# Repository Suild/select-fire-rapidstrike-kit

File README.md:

# select-fire-rapidstrike-kit
Schematics, board files, and firmware for every variant of the Select-fire Rapidstrike Kit.

Buy Link: https://suild.com/shop/4

Grants reliable select-fire control to your Rapidstrike with optional rate of fire control using a knob. Like every other kit, this one is super simple to install and requires no soldering directly onto the board to get everything up and runing in under a minute, even easier than a regular RS mod!

Built-in pusher return and solenoid support makes this kit easily adaptable to any custom 3D-printed blaster. A powerful voltage regulator buck converter, on-board Arduino Nano, and breakout of power rails make this ideal for tinkerers and Makers who want to bring this kit one step farther. And everything is open-source.

I hope you find value in this. I personally learned a lot from open-source projects. I've included a PDF for every schematic and images of the top and bottom for every board so you can view them on mobile and without installing Eagle CAD.

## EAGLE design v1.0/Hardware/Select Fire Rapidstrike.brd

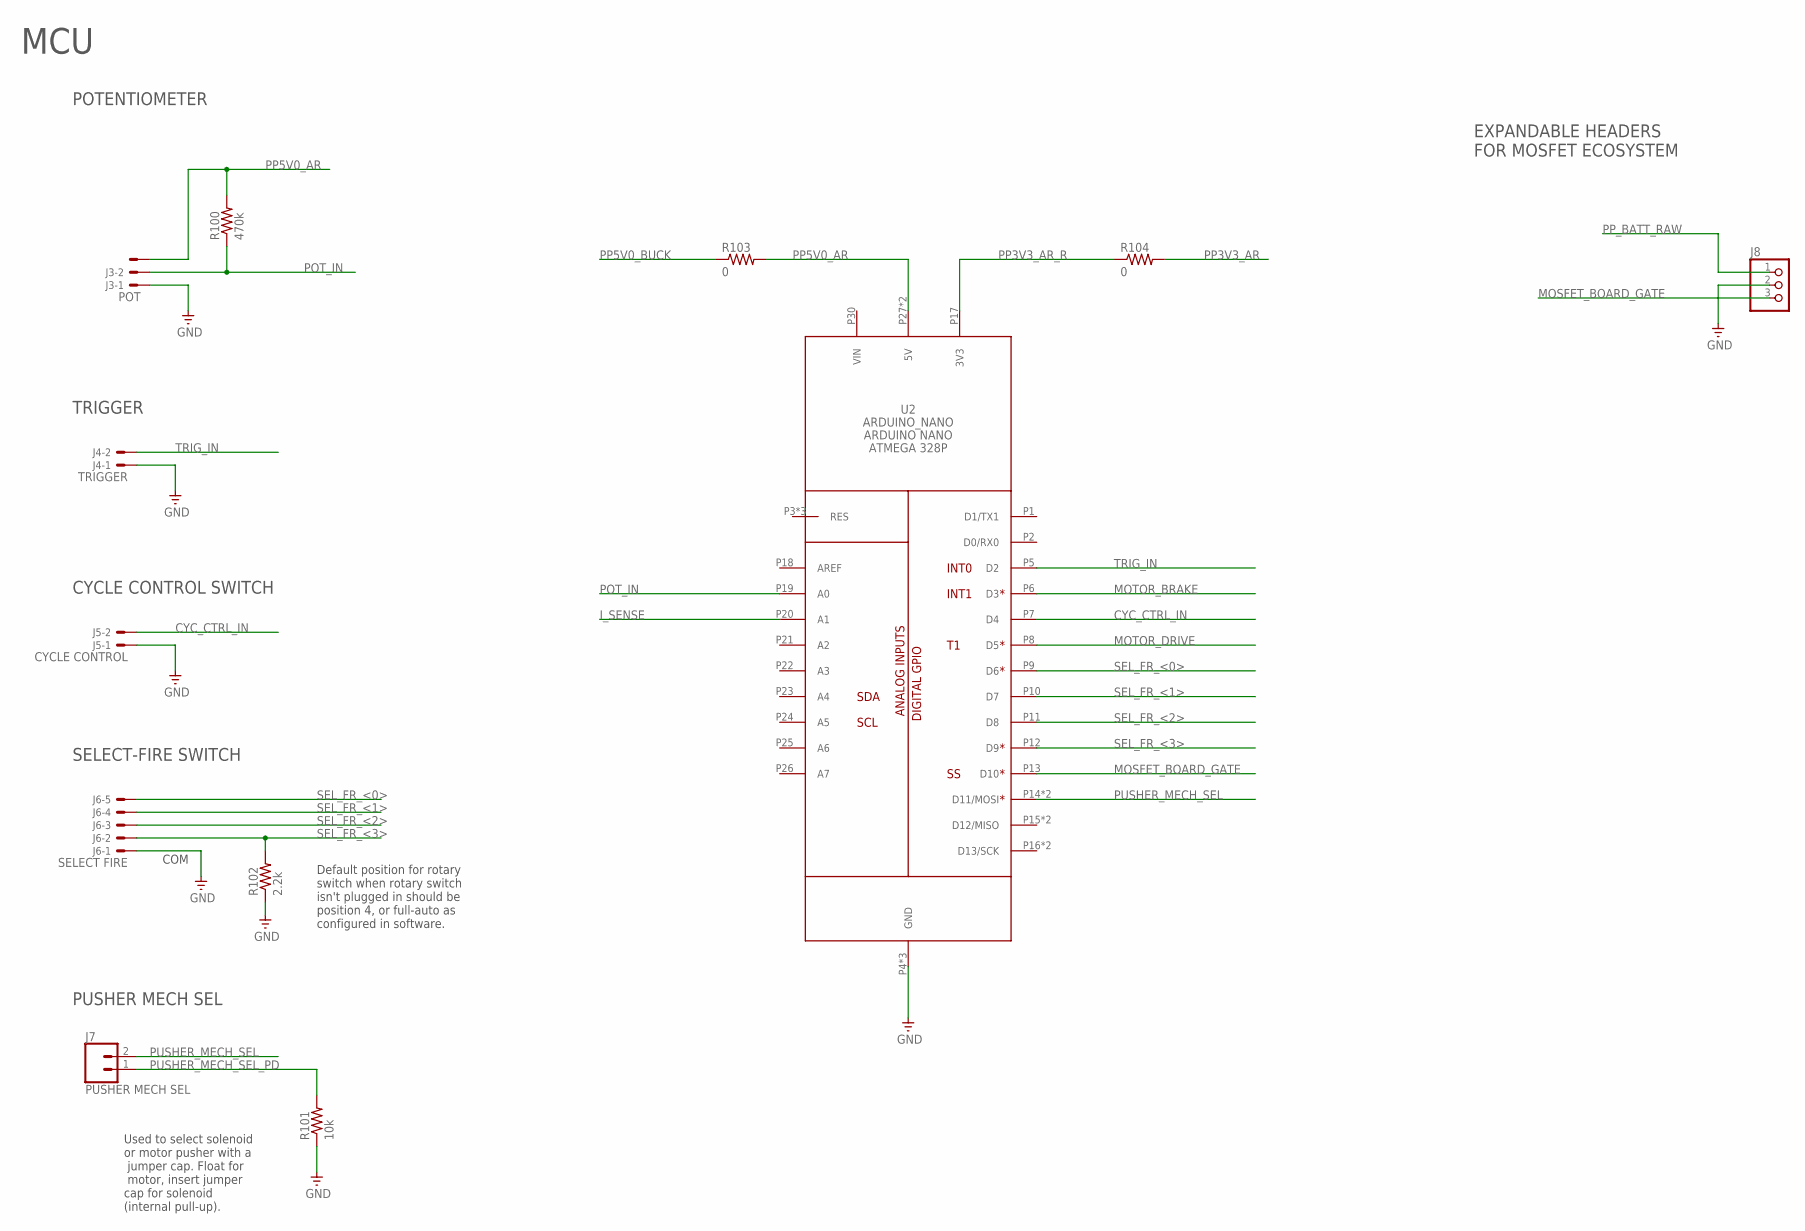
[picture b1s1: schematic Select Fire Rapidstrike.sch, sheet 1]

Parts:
J3: POT; JST-XH-03-PACKAGE-LONG-PAD
J4: TRIGGER; JST-XH-02-PACKAGE-LONG-PAD
J5: CYCLE CONTROL; JST-XH-02-PACKAGE-LONG-PAD
J6: SELECT FIRE; JST-XH-05-PACKAGE-LONG-PAD
J7: PUSHER MECH SEL; 1X02
J8: PINHD-1X3; 1X03
R100: 470k; M0805
R101: 10k; M0805
R102: 2.2k; M0805
R103, R104: 0; M0805
U2: ARDUINO_NANO

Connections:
CYC_CTRL_IN: J5.2, U2.P7 (D4)
GND: J3.1, J4.1, J5.1, J6.1, J8.2, R101.1, R102.1, U2.P4 (GND), U2.P29 (GND), U2.P32 (GND); also elsewhere on the board
I_SENSE: U2.P20 (A1); also elsewhere on the board
MOSFET_BOARD_GATE: J8.3, U2.P13 (D10)
MOTOR_BRAKE: U2.P6 (D3); also elsewhere on the board
MOTOR_DRIVE: U2.P8 (D5); also elsewhere on the board
POT_IN: J3.2, R100.1, U2.P19 (A0)
PP3V3_AR: R104.2; also elsewhere on the board
PP3V3_AR_R: R104.1, U2.P17 (3V3)
PP5V0_AR: J3.3, R100.2, R103.2, U2.P27 (5V), U2.P36 (5V); also elsewhere on the board
PP5V0_BUCK: R103.1; also elsewhere on the board
PP_BATT_RAW: J8.1; also elsewhere on the board
PUSHER_MECH_SEL: J7.2, U2.P14 (D11/MOSI), U2.P34 (D11/MOSI)
PUSHER_MECH_SEL_PD: J7.1, R101.2
SEL_FR_<0>: J6.5, U2.P9 (D6)
SEL_FR_<1>: J6.4, U2.P10 (D7)
SEL_FR_<2>: J6.3, U2.P11 (D8)
SEL_FR_<3>: J6.2, R102.2, U2.P12 (D9)
TRIG_IN: J4.2, U2.P5 (D2)

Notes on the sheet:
MCU
POTENTIOMETER
TRIGGER
CYCLE CONTROL SWITCH
SELECT-FIRE SWITCH
EXPANDABLE HEADERS FOR MOSFET ECOSYSTEM
PUSHER MECH SEL
Default position for rotary switch when rotary switch isn't plugged in should be position 4, or full-auto as configured in software.
Used to select solenoid or motor pusher with a jumper cap. Float for motor, insert jumper cap for solenoid (internal pull-up).
COM

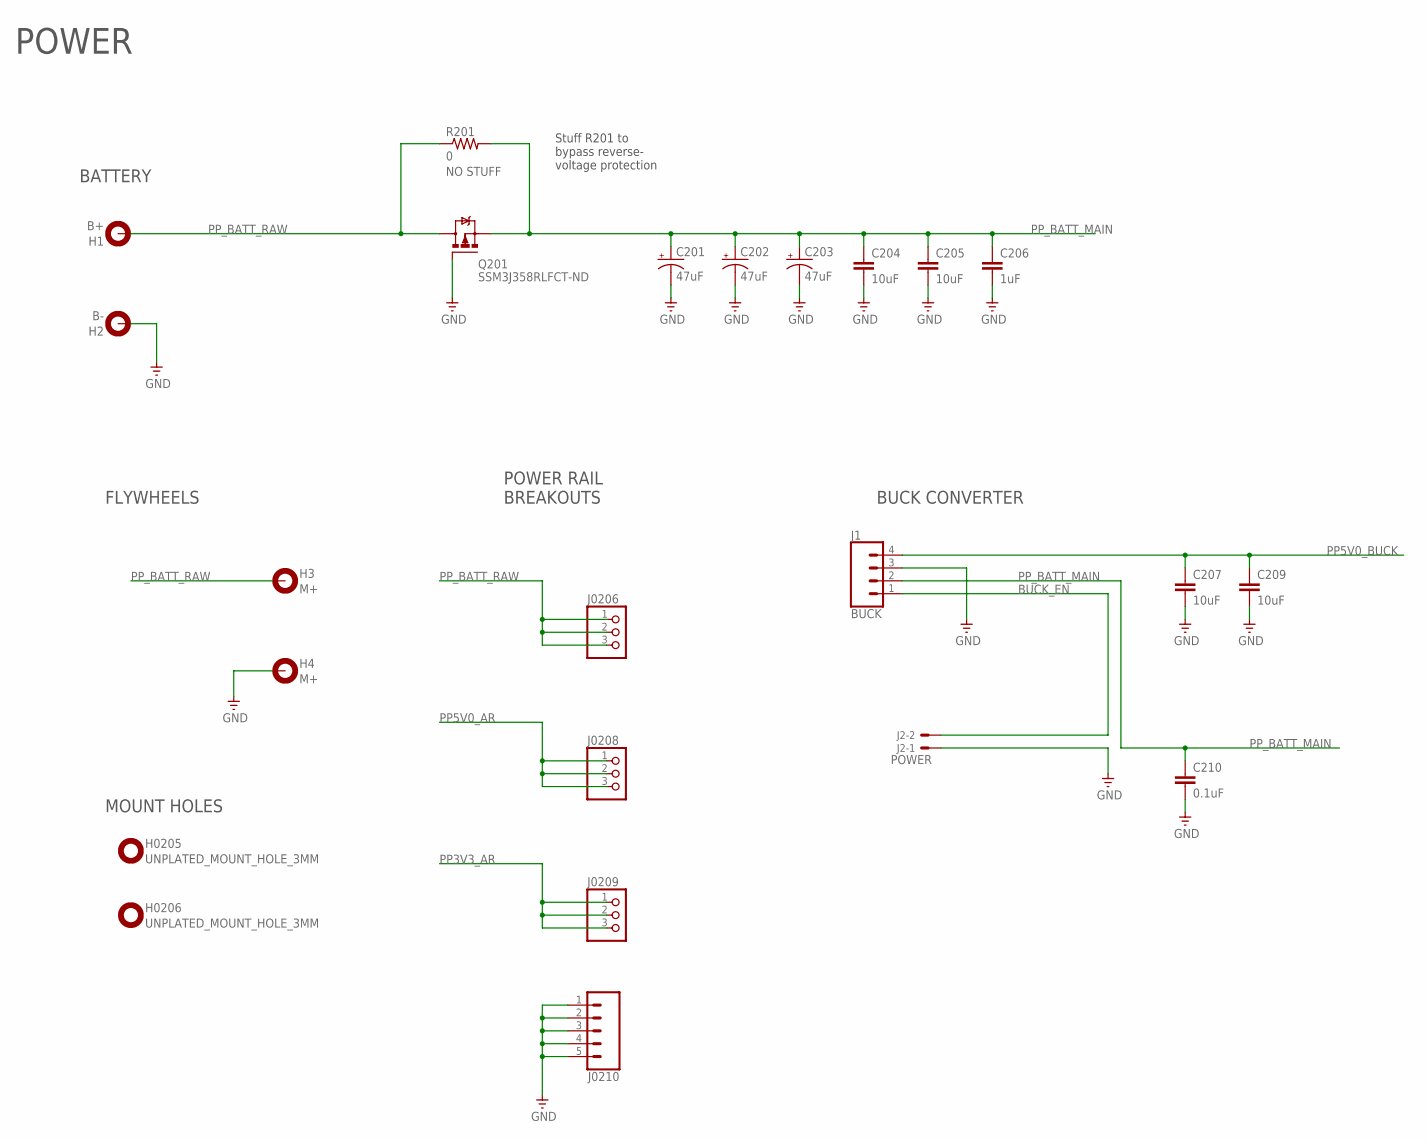
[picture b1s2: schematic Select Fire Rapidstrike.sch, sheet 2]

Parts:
C201, C202, C203: 47uF; E2-5
C204, C205, C207, C209: 10uF; C1206
C206: 1uF; C0805
C210: 0.1uF; C0805
H1: B+; MOUNT-HOLE-2.5MM
H2: B-; MOUNT-HOLE-2.5MM
H3, H4: M+; MOUNT-HOLE-2.5MM
H0205, H0206: UNPLATED_MOUNT_HOLE_3MM
J1: BUCK; 1X04
J2: POWER; JST-XH-02-PACKAGE-LONG-PAD
J0206, J0208, J0209: PINHD-1X3; 1X03
J0210: CONN_05; 1X05
Q201: SSM3J358RLFCT-ND; SOT-23
R201: 0; R1206

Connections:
BUCK_EN: J1.1, J2.2
GND: C201.-, C202.-, C203.-, C204.2, C205.2, C206.2, C207.2, C209.2, C210.2, H2.P$1, H4.P$1, J1.3, J2.1, J0210.1, J0210.2, J0210.3, J0210.4, J0210.5, Q201.1 (G); also elsewhere on the board
PP3V3_AR: J0209.1, J0209.2, J0209.3; also elsewhere on the board
PP5V0_AR: J0208.1, J0208.2, J0208.3; also elsewhere on the board
PP5V0_BUCK: C207.1, C209.1, J1.4; also elsewhere on the board
PP_BATT_MAIN: C201.+, C202.+, C203.+, C204.1, C205.1, C206.1, C210.1, J1.2, Q201.2 (S), R201.2
PP_BATT_RAW: H1.P$1, H3.P$1, J0206.1, J0206.2, J0206.3, Q201.3 (D), R201.1; also elsewhere on the board

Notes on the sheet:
BUCK CONVERTER
BATTERY
FLYWHEELS
MOUNT HOLES
POWER
POWER RAIL BREAKOUTS
Stuff R201 to bypass reverse- voltage protection

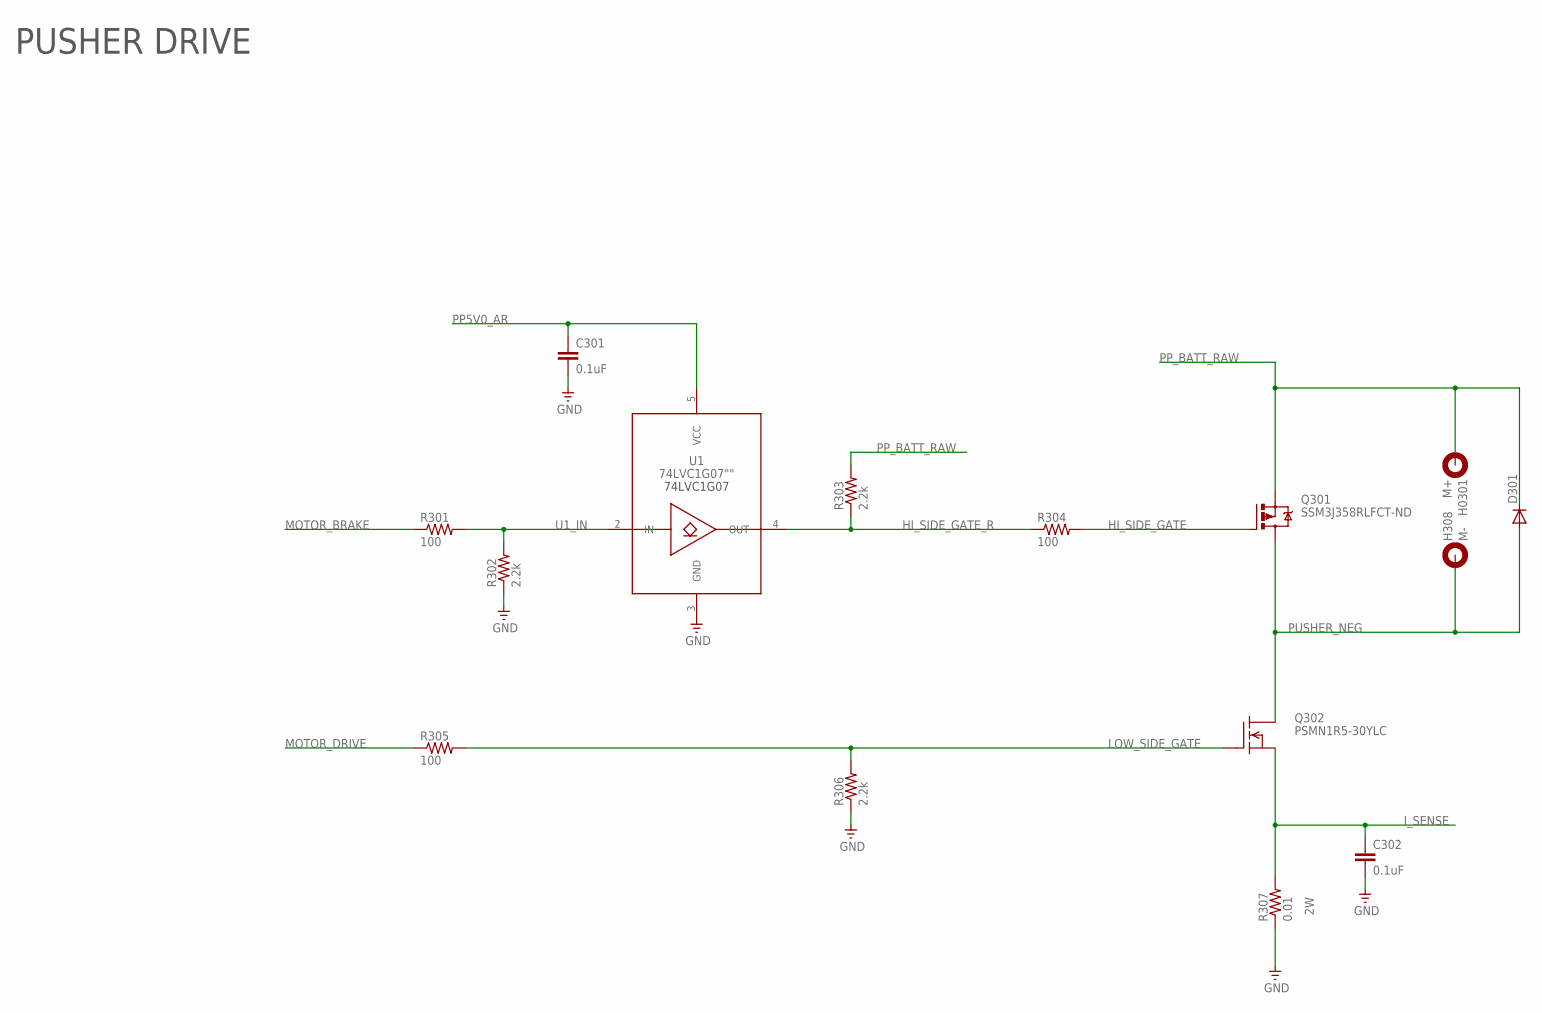
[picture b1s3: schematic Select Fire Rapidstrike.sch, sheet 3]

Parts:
C301, C302: 0.1uF; C0805
D301: S2A; DO214AA
H0301: M+; MOUNT-HOLE-2.5MM
H308: M-; MOUNT-HOLE-2.5MM
Q301: SSM3J358RLFCT-ND; SOT-23
Q302: PSMN1R5-30YLC; TO127P600X120-5N
R301, R304, R305: 100; M0805
R302, R303, R306: 2.2k; M0805
R307: 0.01; R2512
U1: 74LVC1G07""; SOT353

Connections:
GND: C301.2, C302.2, R302.1, R306.1, R307.1, U1.3 (GND); also elsewhere on the board
HI_SIDE_GATE: Q301.1 (G), R304.2
HI_SIDE_GATE_R: R303.1, R304.1, U1.4 (OUT)
I_SENSE: C302.1, Q302.1 (S), Q302.2 (S), Q302.3 (S), R307.2; also elsewhere on the board
LOW_SIDE_GATE: Q302.4 (G), R305.2, R306.2
MOTOR_BRAKE: R301.1; also elsewhere on the board
MOTOR_DRIVE: R305.1; also elsewhere on the board
PP5V0_AR: C301.1, U1.5 (VCC); also elsewhere on the board
PP_BATT_RAW: D301.C, H0301.P$1, Q301.2 (S), R303.2; also elsewhere on the board
PUSHER_NEG: D301.A, H308.P$1, Q301.3 (D), Q302.5 (D)
U1_IN: R301.2, R302.2, U1.2 (IN)

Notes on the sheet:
PUSHER DRIVE

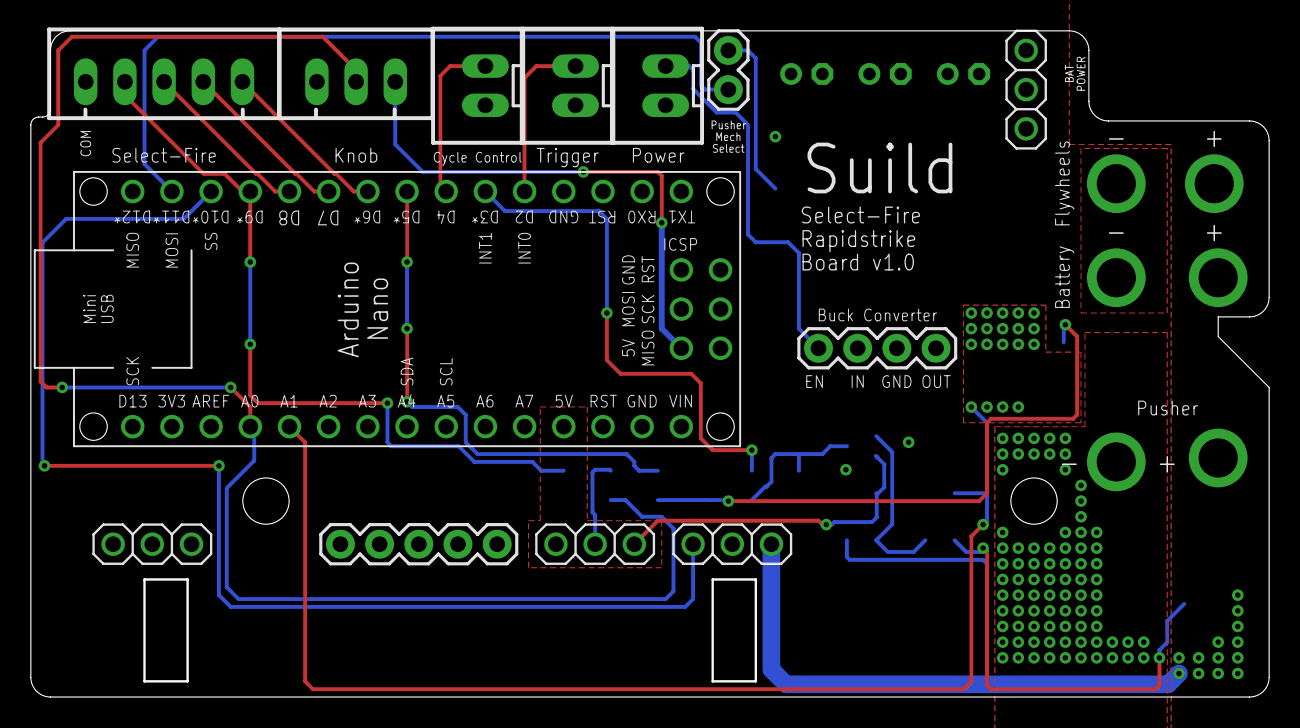
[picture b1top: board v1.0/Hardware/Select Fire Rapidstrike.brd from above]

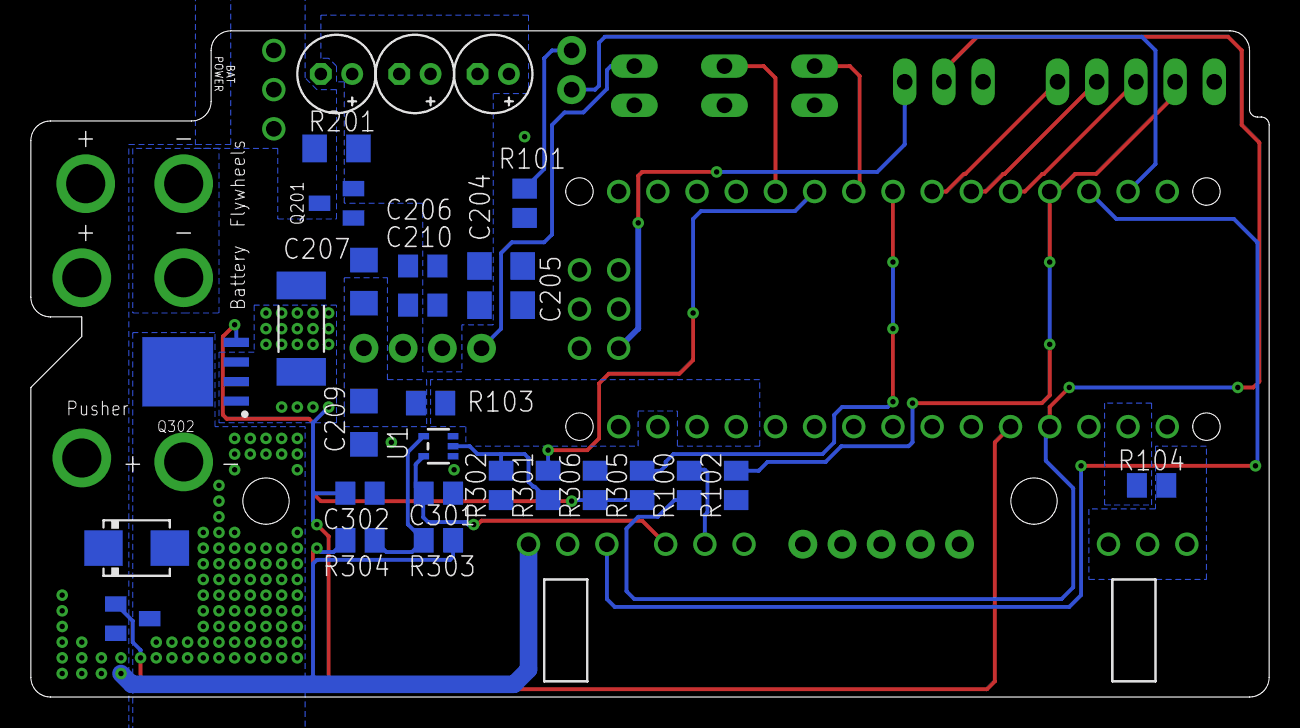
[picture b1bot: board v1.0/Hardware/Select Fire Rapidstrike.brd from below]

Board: 2 copper layers, 80.3 x 43.2 mm, 50 parts (30 on the bottom side), 26 nets.

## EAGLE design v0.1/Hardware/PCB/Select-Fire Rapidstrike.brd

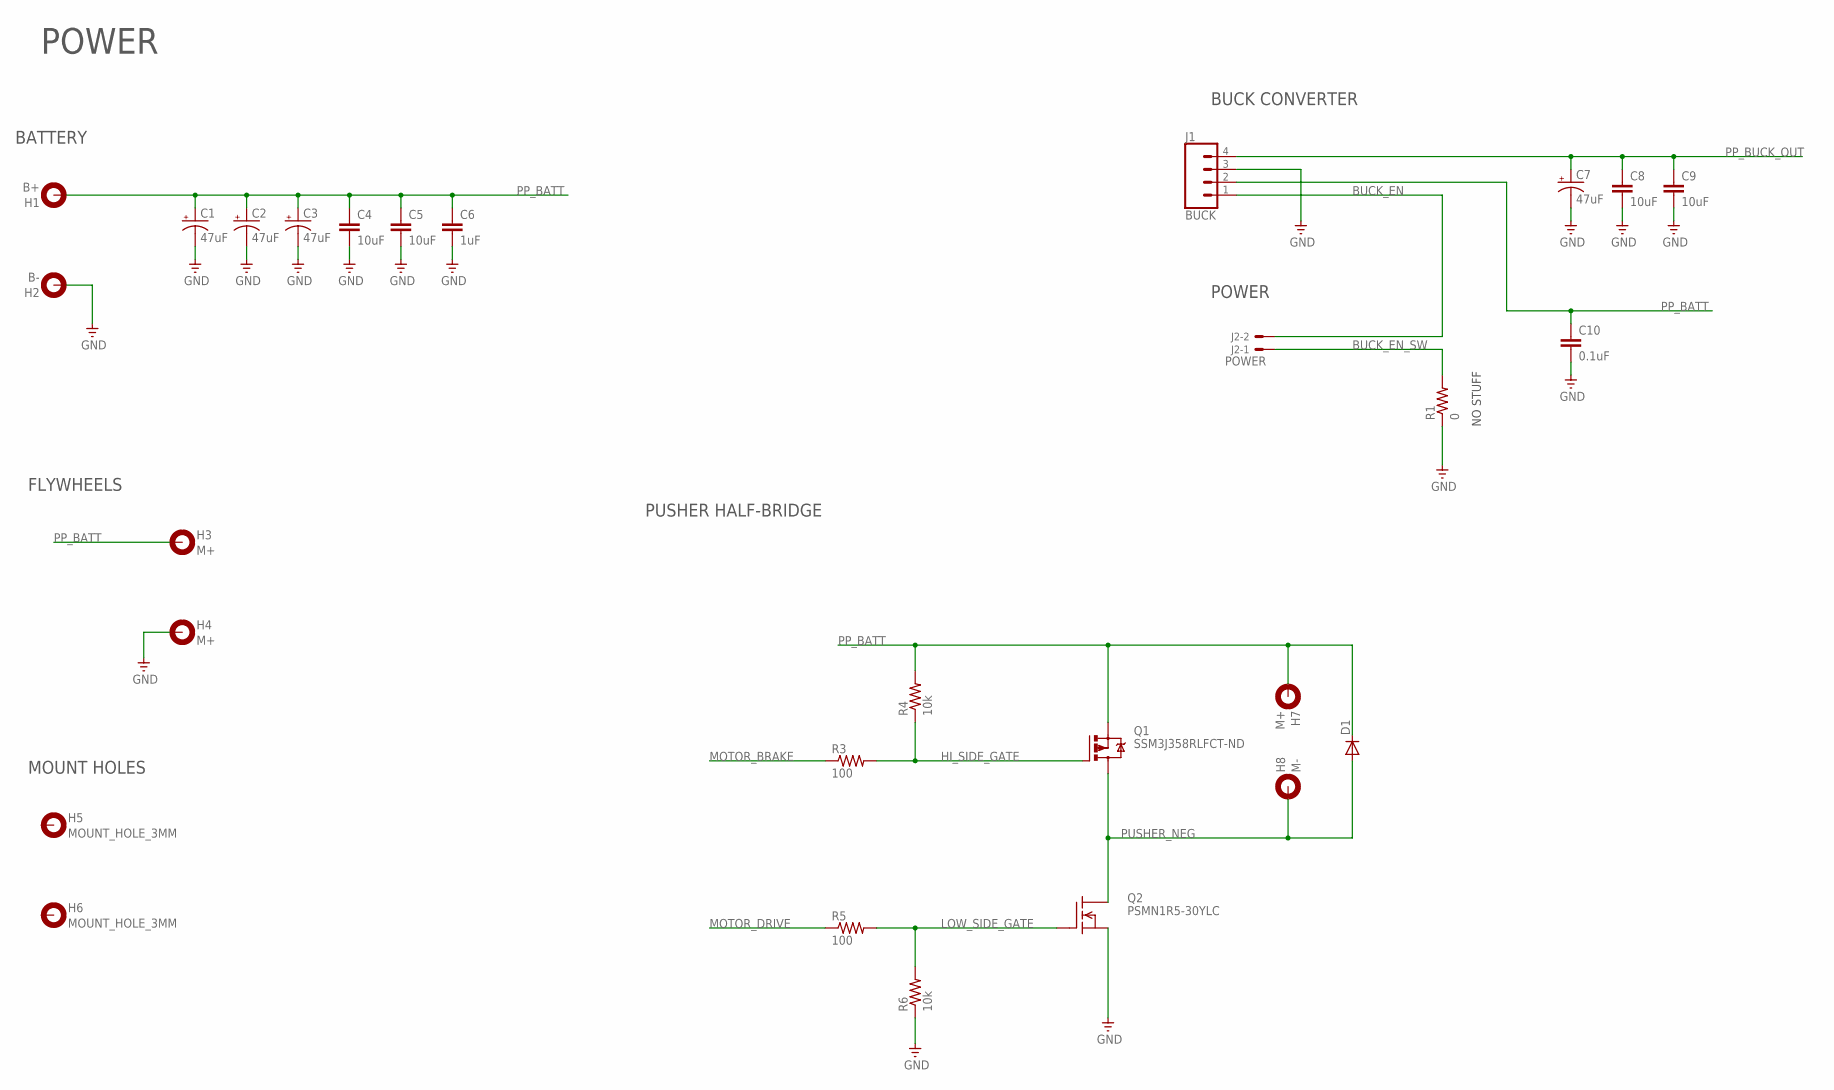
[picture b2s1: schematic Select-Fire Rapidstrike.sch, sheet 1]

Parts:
C1, C2, C3, C7: 47uF; E2-5
C4, C5, C8, C9: 10uF; C1206
C6: 1uF; C0805
C10: 0.1uF; C0805
D1: S2A; DO214AA
H1: B+; MOUNT-HOLE-2.5MM
H2: B-; MOUNT-HOLE-2.5MM
H3, H4, H7: M+; MOUNT-HOLE-2.5MM
H5, H6: MOUNT_HOLE_3MM
H8: M-; MOUNT-HOLE-2.5MM
J1: BUCK; 1X04
J2: POWER; JST-XH-02-PACKAGE-LONG-PAD
Q1: SSM3J358RLFCT-ND; SOT-23
Q2: PSMN1R5-30YLC; TO127P600X120-5N
R1: 0; M0805
R3, R5: 100; M0805
R4, R6: 10k; M0805

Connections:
BUCK_EN: J1.1, J2.2
BUCK_EN_SW: J2.1, R1.2
GND: C1.-, C2.-, C3.-, C4.2, C5.2, C6.2, C7.-, C8.2, C9.2, C10.2, H2.P$1, H4.P$1, J1.3, Q2.1 (S), Q2.2 (S), Q2.3 (S), R1.1, R6.1; also elsewhere on the board
HI_SIDE_GATE: Q1.1 (G), R3.2, R4.1
LOW_SIDE_GATE: Q2.4 (G), R5.2, R6.2
MOTOR_BRAKE: R3.1; also elsewhere on the board
MOTOR_DRIVE: R5.1; also elsewhere on the board
PP_BATT: C1.+, C2.+, C3.+, C4.1, C5.1, C6.1, C10.1, D1.C, H1.P$1, H3.P$1, H7.P$1, J1.2, Q1.2 (S), R4.2; also elsewhere on the board
PP_BUCK_OUT: C7.+, C8.1, C9.1, J1.4; also elsewhere on the board
PUSHER_NEG: D1.A, H8.P$1, Q1.3 (D), Q2.5 (D)

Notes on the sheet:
PUSHER HALF-BRIDGE
NO STUFF
BUCK CONVERTER
POWER
BATTERY
FLYWHEELS
MOUNT HOLES

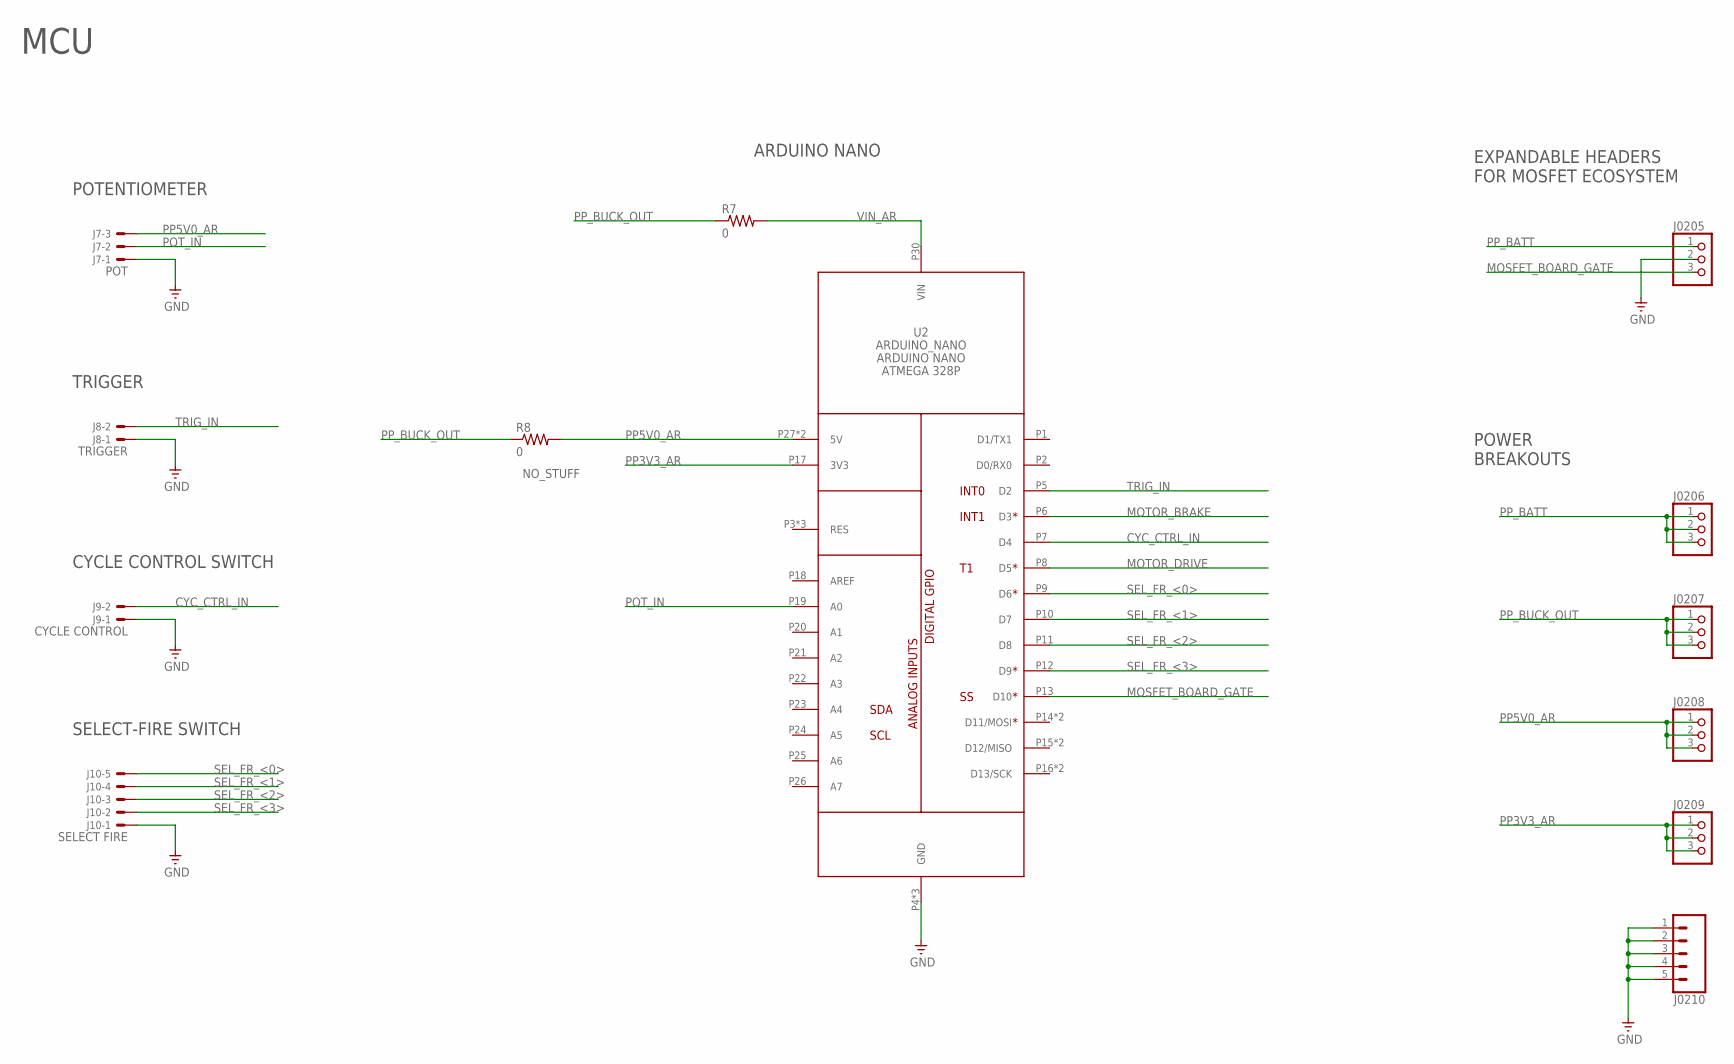
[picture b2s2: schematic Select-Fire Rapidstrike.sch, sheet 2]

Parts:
J7: POT; JST-XH-03-PACKAGE-LONG-PAD
J8: TRIGGER; JST-XH-02-PACKAGE-LONG-PAD
J9: CYCLE CONTROL; JST-XH-02-PACKAGE-LONG-PAD
J10: SELECT FIRE; JST-XH-05-PACKAGE-LONG-PAD
J0205, J0206, J0207, J0208, J0209: PINHD-1X3; 1X03
J0210: CONN_05; 1X05
R7, R8: 0; M0805
U2: ARDUINO_NANO

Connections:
CYC_CTRL_IN: J9.2, U2.P7 (D4)
GND: J7.1, J8.1, J9.1, J10.1, J0205.2, J0210.1, J0210.2, J0210.3, J0210.4, J0210.5, U2.P4 (GND), U2.P29 (GND), U2.P32 (GND); also elsewhere on the board
MOSFET_BOARD_GATE: J0205.3, U2.P13 (D10)
MOTOR_BRAKE: U2.P6 (D3); also elsewhere on the board
MOTOR_DRIVE: U2.P8 (D5); also elsewhere on the board
POT_IN: J7.2, U2.P19 (A0)
PP3V3_AR: J0209.1, J0209.2, J0209.3, U2.P17 (3V3)
PP5V0_AR: J7.3, J0208.1, J0208.2, J0208.3, R8.2, U2.P27 (5V), U2.P36 (5V)
PP_BATT: J0205.1, J0206.1, J0206.2, J0206.3; also elsewhere on the board
PP_BUCK_OUT: J0207.1, J0207.2, J0207.3, R7.1, R8.1; also elsewhere on the board
SEL_FR_<0>: J10.5, U2.P9 (D6)
SEL_FR_<1>: J10.4, U2.P10 (D7)
SEL_FR_<2>: J10.3, U2.P11 (D8)
SEL_FR_<3>: J10.2, U2.P12 (D9)
TRIG_IN: J8.2, U2.P5 (D2)
VIN_AR: R7.2, U2.P30 (VIN)

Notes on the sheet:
MCU
POTENTIOMETER
TRIGGER
CYCLE CONTROL SWITCH
ARDUINO NANO
SELECT-FIRE SWITCH
EXPANDABLE HEADERS FOR MOSFET ECOSYSTEM
POWER BREAKOUTS

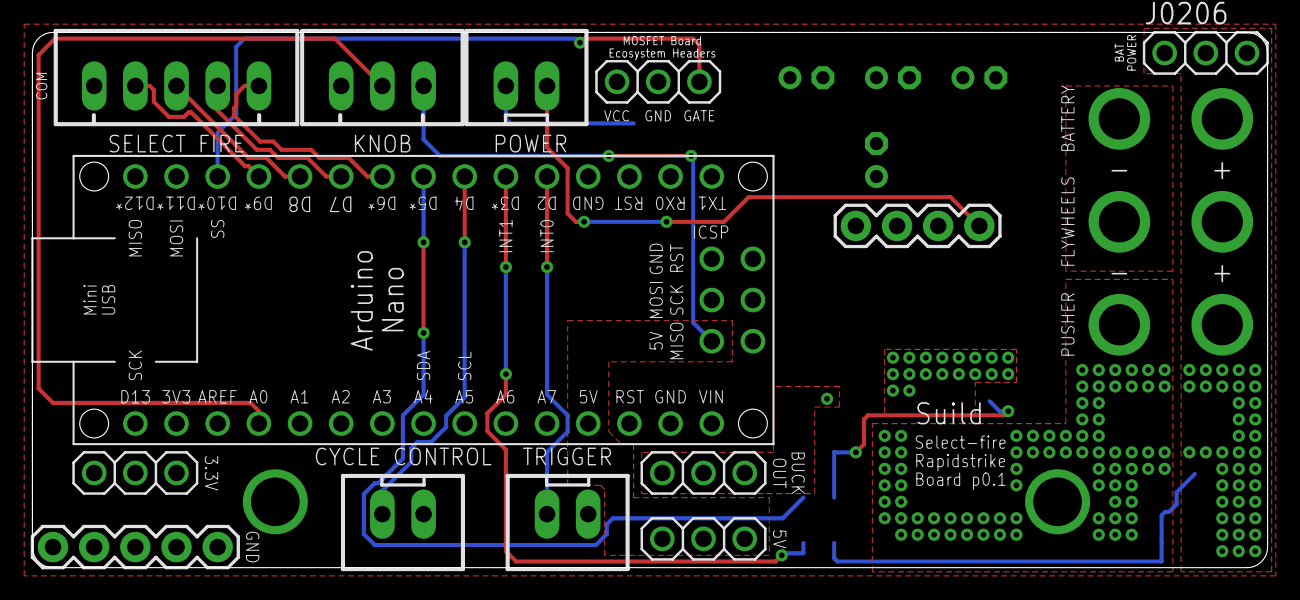
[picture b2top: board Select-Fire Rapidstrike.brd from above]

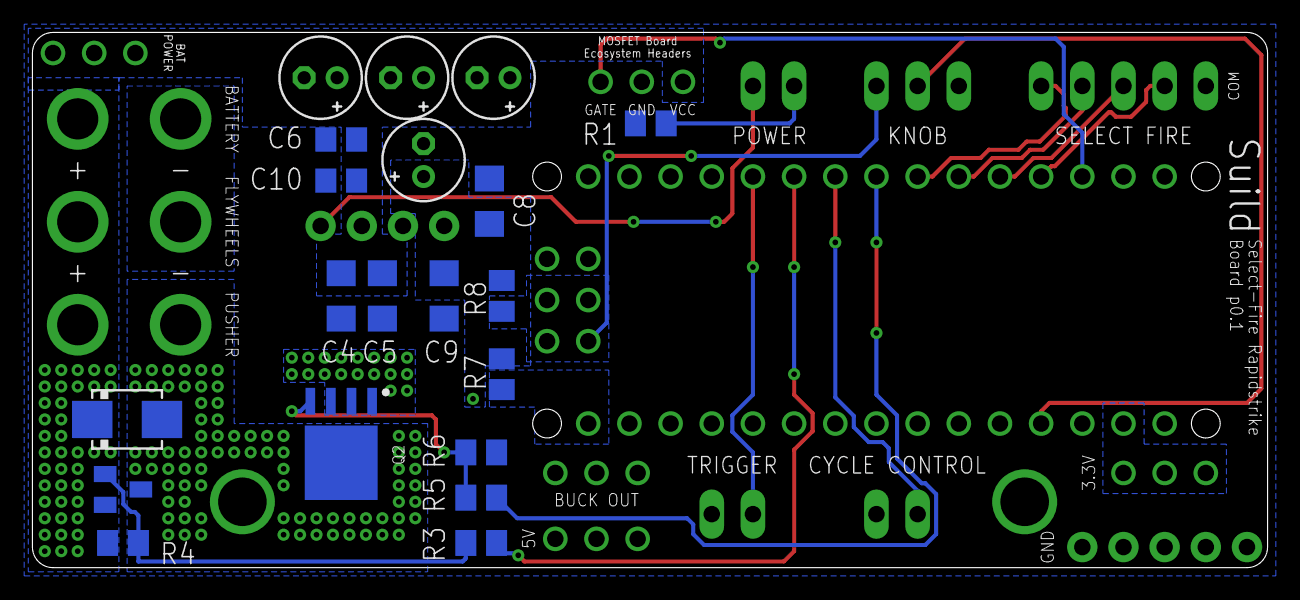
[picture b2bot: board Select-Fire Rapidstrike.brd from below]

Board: 2 copper layers, 76.2 x 33.0 mm, 41 parts (20 on the bottom side), 21 nets.

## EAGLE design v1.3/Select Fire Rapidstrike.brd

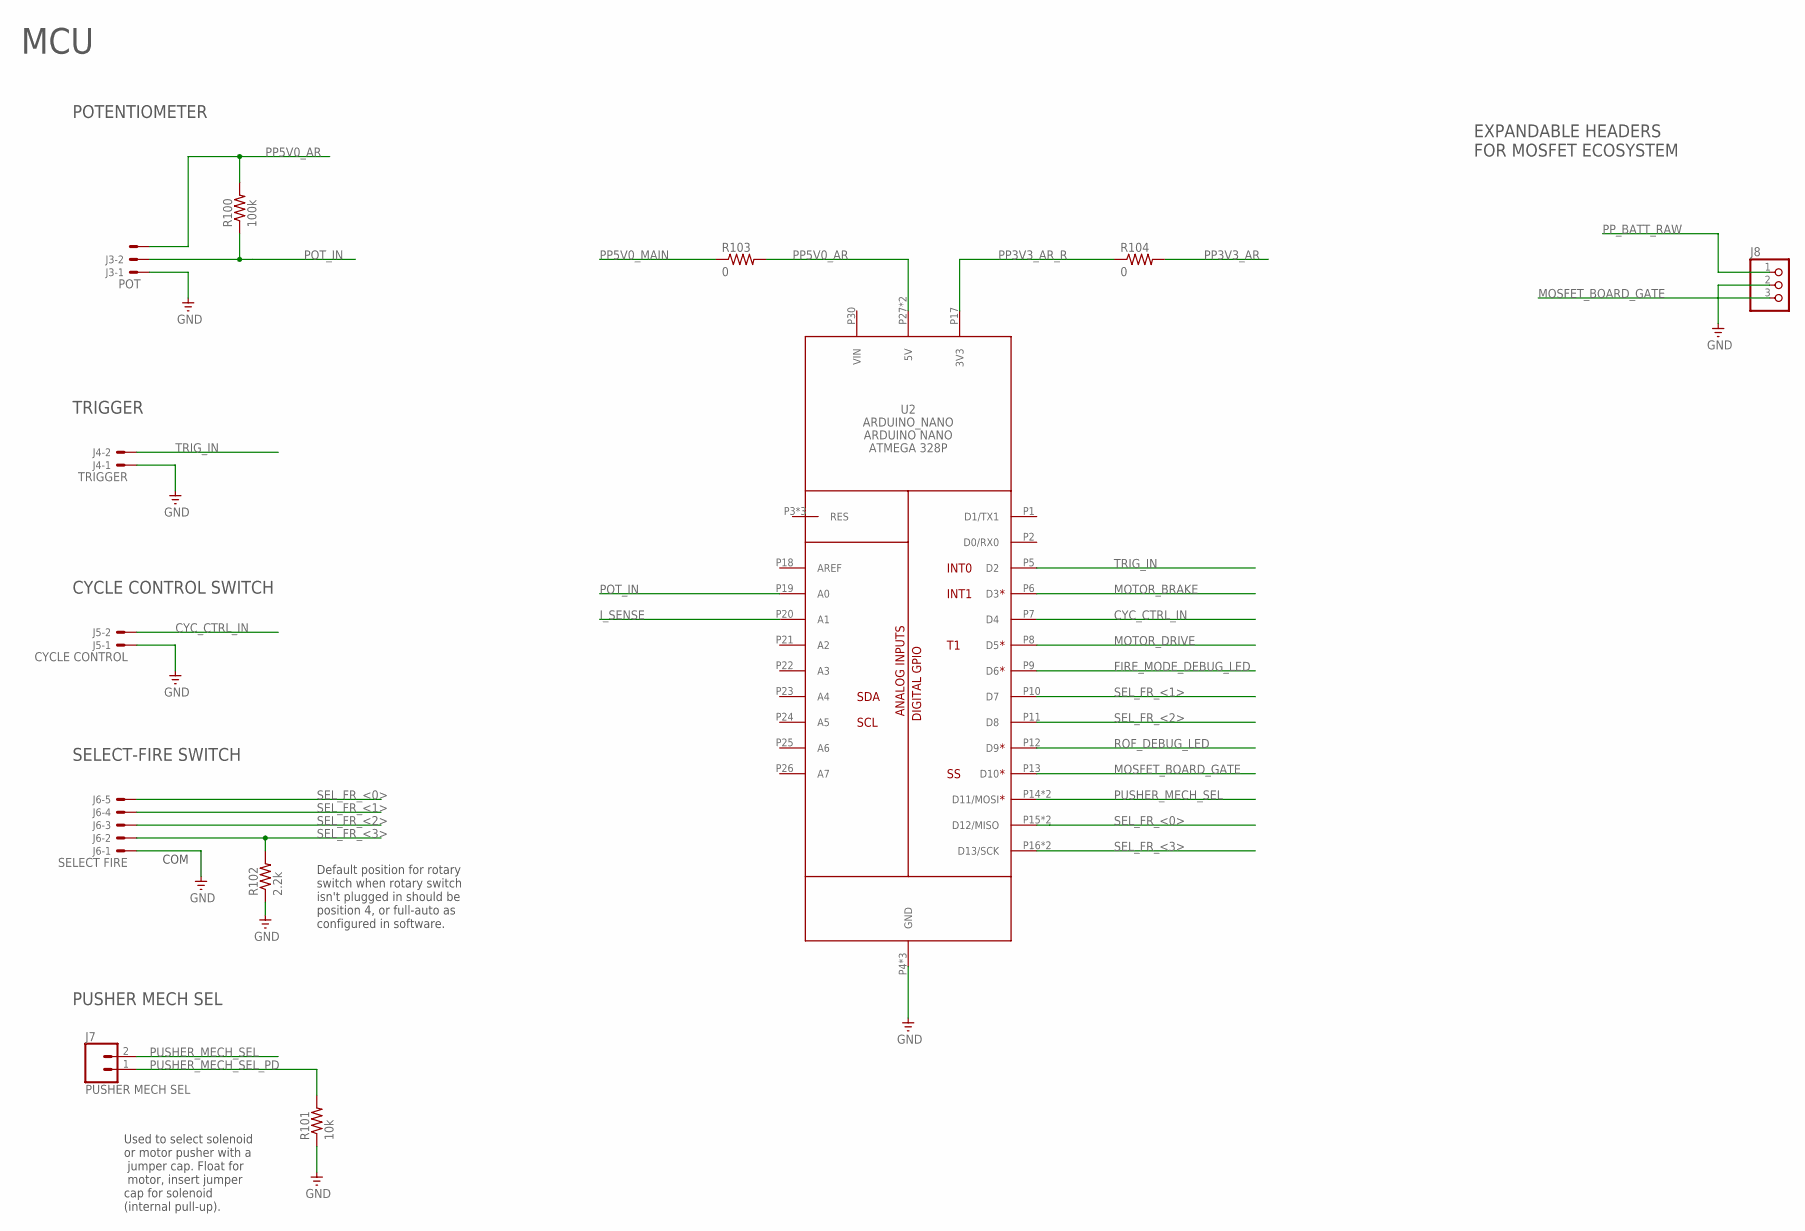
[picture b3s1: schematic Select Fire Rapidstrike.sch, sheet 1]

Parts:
J3: POT; JST-XH-03-PACKAGE-LONG-PAD
J4: TRIGGER; JST-XH-02-PACKAGE-LONG-PAD
J5: CYCLE CONTROL; JST-XH-02-PACKAGE-LONG-PAD
J6: SELECT FIRE; JST-XH-05-PACKAGE-LONG-PAD
J7: PUSHER MECH SEL; 1X02
J8: PINHD-1X3; 1X03
R100: 100k; M0805
R101: 10k; M0805
R102: 2.2k; M0805
R103, R104: 0; M0805
U2: ARDUINO_NANO

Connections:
CYC_CTRL_IN: J5.2, U2.P7 (D4); also elsewhere on the board
FIRE_MODE_DEBUG_LED: U2.P9 (D6); also elsewhere on the board
GND: J3.1, J4.1, J5.1, J6.1, J8.2, R101.1, R102.1, U2.P4 (GND), U2.P29 (GND), U2.P32 (GND); also elsewhere on the board
I_SENSE: U2.P20 (A1); also elsewhere on the board
MOSFET_BOARD_GATE: J8.3, U2.P13 (D10)
MOTOR_BRAKE: U2.P6 (D3); also elsewhere on the board
MOTOR_DRIVE: U2.P8 (D5); also elsewhere on the board
POT_IN: J3.2, R100.1, U2.P19 (A0)
PP3V3_AR: R104.2; also elsewhere on the board
PP3V3_AR_R: R104.1, U2.P17 (3V3)
PP5V0_AR: J3.3, R100.2, R103.2, U2.P27 (5V), U2.P36 (5V); also elsewhere on the board
PP5V0_MAIN: R103.1; also elsewhere on the board
PP_BATT_RAW: J8.1; also elsewhere on the board
PUSHER_MECH_SEL: J7.2, U2.P14 (D11/MOSI), U2.P34 (D11/MOSI)
PUSHER_MECH_SEL_PD: J7.1, R101.2
ROF_DEBUG_LED: U2.P12 (D9); also elsewhere on the board
SEL_FR_<0>: J6.5, U2.P15 (D12/MISO), U2.P35 (D12/MISO)
SEL_FR_<1>: J6.4, U2.P10 (D7)
SEL_FR_<2>: J6.3, U2.P11 (D8)
SEL_FR_<3>: J6.2, R102.2, U2.P16 (D13/SCK), U2.P33 (D13/SCK)
TRIG_IN: J4.2, U2.P5 (D2); also elsewhere on the board

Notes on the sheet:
MCU
POTENTIOMETER
TRIGGER
CYCLE CONTROL SWITCH
SELECT-FIRE SWITCH
EXPANDABLE HEADERS FOR MOSFET ECOSYSTEM
PUSHER MECH SEL
Default position for rotary switch when rotary switch isn't plugged in should be position 4, or full-auto as configured in software.
Used to select solenoid or motor pusher with a jumper cap. Float for motor, insert jumper cap for solenoid (internal pull-up).
COM

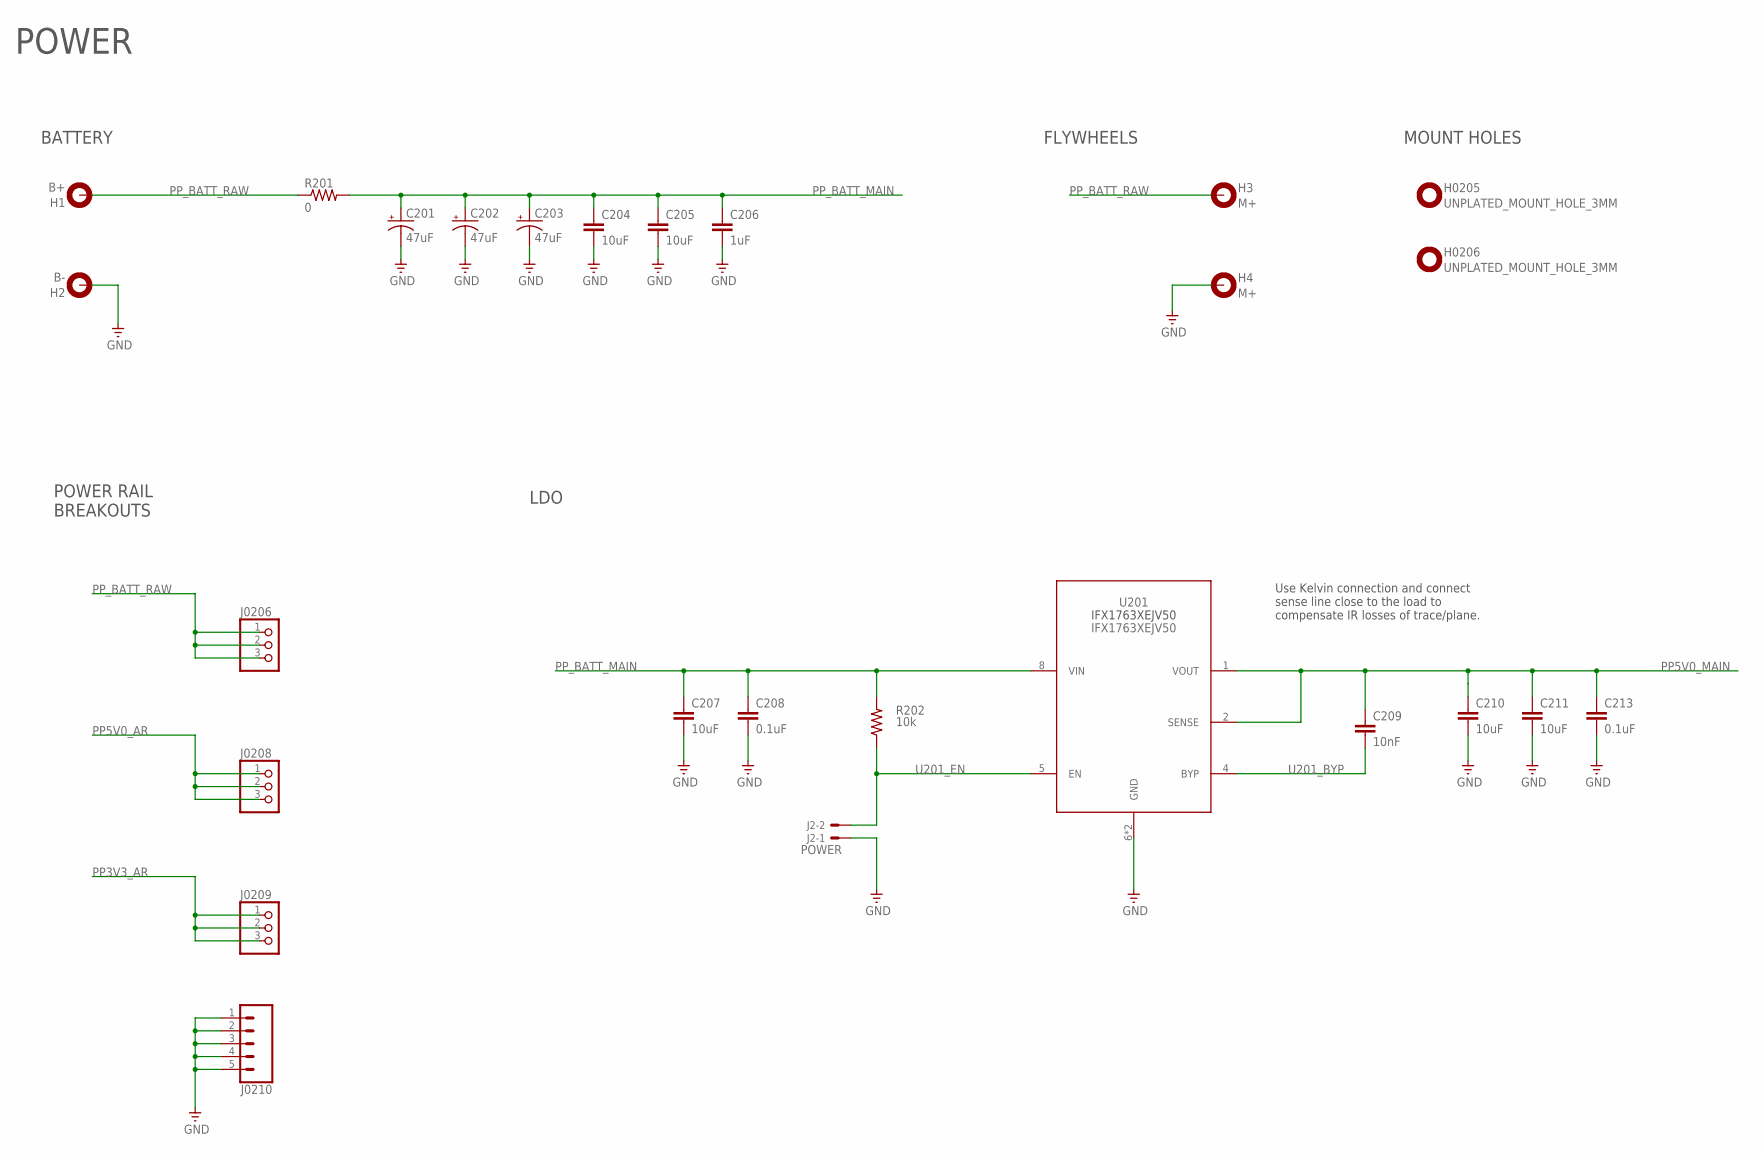
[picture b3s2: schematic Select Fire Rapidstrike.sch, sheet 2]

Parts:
C201, C202, C203: 47uF; E2-5
C204, C205, C207, C210, C211: 10uF; C1206
C206: 1uF; C0805
C208, C213: 0.1uF; C0805
C209: 10nF; C0805
H1: B+; MOUNT-HOLE-2.5MM
H2: B-; MOUNT-HOLE-2.5MM
H3, H4: M+; MOUNT-HOLE-2.5MM
H0205, H0206: UNPLATED_MOUNT_HOLE_3MM
J2: POWER; JST-XH-02-PACKAGE-LONG-PAD
J0206, J0208, J0209: PINHD-1X3; 1X03
J0210: CONN_05; 1X05
R201: 0; M0805
R202: 10k; M0805
U201: IFX1763XEJV50; PG-DSO-8

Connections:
GND: C201.-, C202.-, C203.-, C204.2, C205.2, C206.2, C207.2, C208.2, C210.2, C211.2, C213.2, H2.P$1, H4.P$1, J2.1, J0210.1, J0210.2, J0210.3, J0210.4, J0210.5, U201.6 (GND), U201.BODY (GND); also elsewhere on the board
PP3V3_AR: J0209.1, J0209.2, J0209.3; also elsewhere on the board
PP5V0_AR: J0208.1, J0208.2, J0208.3; also elsewhere on the board
PP5V0_MAIN: C209.1, C210.1, C211.1, C213.1, U201.1 (VOUT), U201.2 (SENSE); also elsewhere on the board
PP_BATT_MAIN: C201.+, C202.+, C203.+, C204.1, C205.1, C206.1, C207.1, C208.1, R201.2, R202.2, U201.8 (VIN)
PP_BATT_RAW: H1.P$1, H3.P$1, J0206.1, J0206.2, J0206.3, R201.1; also elsewhere on the board
U201_BYP: C209.2, U201.4 (BYP)
U201_EN: J2.2, R202.1, U201.5 (EN)

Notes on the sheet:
BATTERY
FLYWHEELS
MOUNT HOLES
POWER
POWER RAIL BREAKOUTS
LDO
Use Kelvin connection and connect sense line close to the load to compensate IR losses of trace/plane.

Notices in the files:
parts and their libraries:
SparkFun-Connectors: Licensing: Creative Commons ShareAlike 4.0 International - https://creativecommons.org/licenses/by-sa/4.0
